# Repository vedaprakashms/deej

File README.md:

# deejCH

deejch is an **open-source hardware volume mixer** for Windows and Linux PCs. It lets you use real-life sliders (like a DJ!) to **seamlessly control the volumes of different apps** (such as your music player, the game you're playing and your voice chat session) without having to stop what you're doing.

This is hardware port of deej, but uses a completely new Lowcost IC CH552G. the entire cost would be less than $5 or ₹500.

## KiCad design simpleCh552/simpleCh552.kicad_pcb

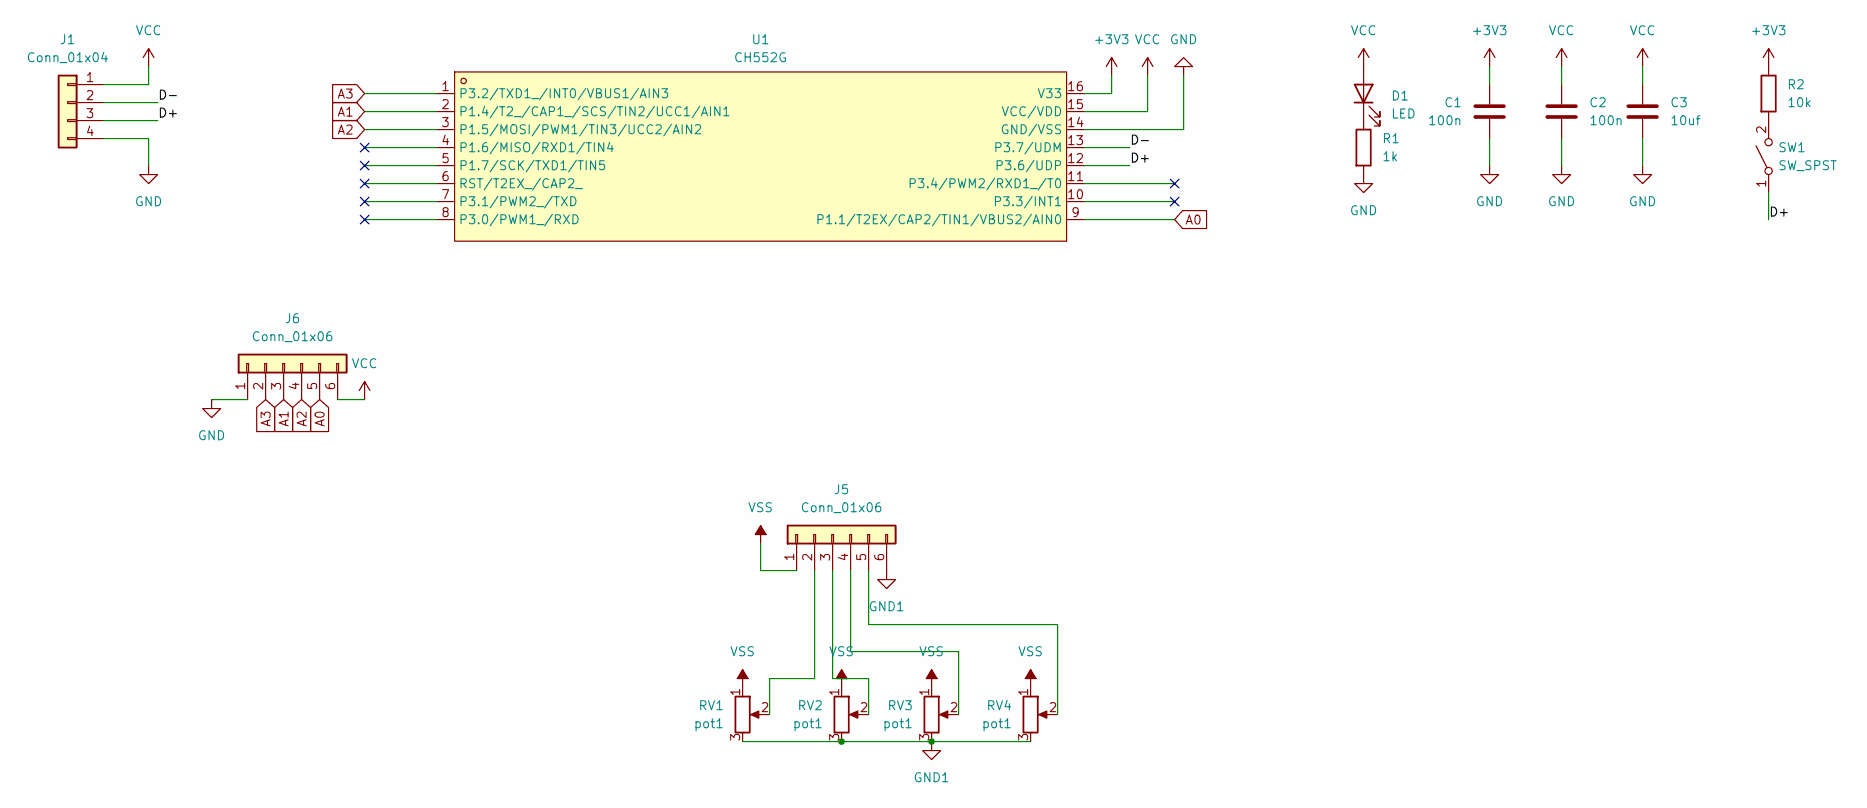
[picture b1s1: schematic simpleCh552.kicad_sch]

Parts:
C1, C2: 100n; C_0603_1608Metric
C3: 10uf; C_0805_2012Metric
D1: LED; LED_1206_3216Metric
J1: Conn_01x04; PinSocket_1x04_P2.54mm_Vertical
J5, J6: Conn_01x06; SolderWire-0.1sqmm_1x06_P3.6mm_D0.4mm_OD1mm
R1: 1k; R_1206_3216Metric
R2: 10k; R_1206_3216Metric
RV1, RV2, RV3, RV4: pot1; Potentiometer_Omeg_PC16BU_Vertical
SW1: SW_SPST; SW_Tactile_SPST_NO_Straight_CK_PTS636Sx25SMTRLFS
U1: CH552G; SOP-16_L10.0-W3.9-P1.27-LS6.0-BL; LCSC Part C111292

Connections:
+3V3: C1.1, R2.1, U1.16 (V33)
/D+: J1.3, SW1.1 (A), U1.12 (P3.6/UDP)
/D-: J1.2, U1.13 (P3.7/UDM)
A0: J6.5, U1.9 (P1.1/T2EX/CAP2/TIN1/VBUS2/AIN0)
A1: J6.3, U1.2 (P1.4/T2_/CAP1_/SCS/TIN2/UCC1/AIN1)
A2: J6.4, U1.3 (P1.5/MOSI/PWM1/TIN3/UCC2/AIN2)
A3: J6.2, U1.1 (P3.2/TXD1_/INT0/VBUS1/AIN3)
GND: C1.2, C2.2, C3.2, J1.4, J6.1, R1.2, U1.14 (GND/VSS)
GND1: J5.6, RV1.3, RV2.3, RV3.3, RV4.3
unnamed: D1.1 (K), R1.1
unnamed: J5.2, RV1.2
unnamed: J5.3, RV2.2
unnamed: J5.4, RV3.2
unnamed: J5.5, RV4.2
unnamed: R2.2, SW1.2 (B)
VCC: C2.1, C3.1, D1.2 (A), J1.1, J6.6, U1.15 (VCC/VDD)
VSS: J5.1, RV1.1, RV2.1, RV3.1, RV4.1

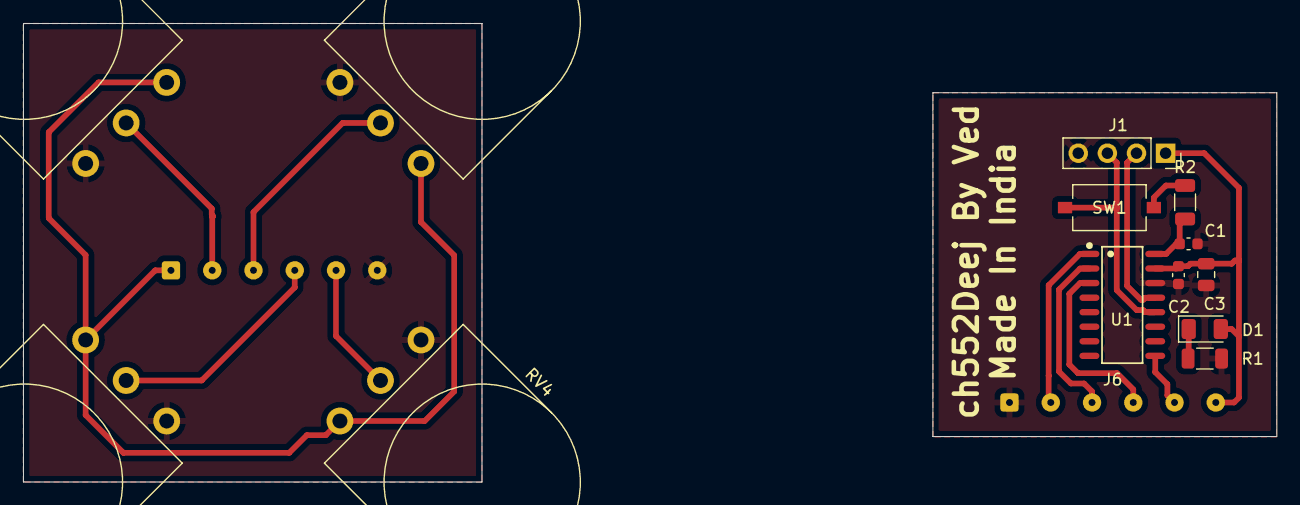
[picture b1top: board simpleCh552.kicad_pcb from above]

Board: 2 copper layers, 109.3 x 40.0 mm, 15 parts (1 on the bottom side), 17 nets.

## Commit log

2025-12-16 Updated with MicroUSB link
    Microsub board ready V1
2025-12-22 update
    update
2026-01-01 updated with pot
2026-01-03 Rename project to deejCH and add hardware details
    Updated project name from 'deej' to 'deejCH' and added information about a new hardware port using the CH552G IC.
